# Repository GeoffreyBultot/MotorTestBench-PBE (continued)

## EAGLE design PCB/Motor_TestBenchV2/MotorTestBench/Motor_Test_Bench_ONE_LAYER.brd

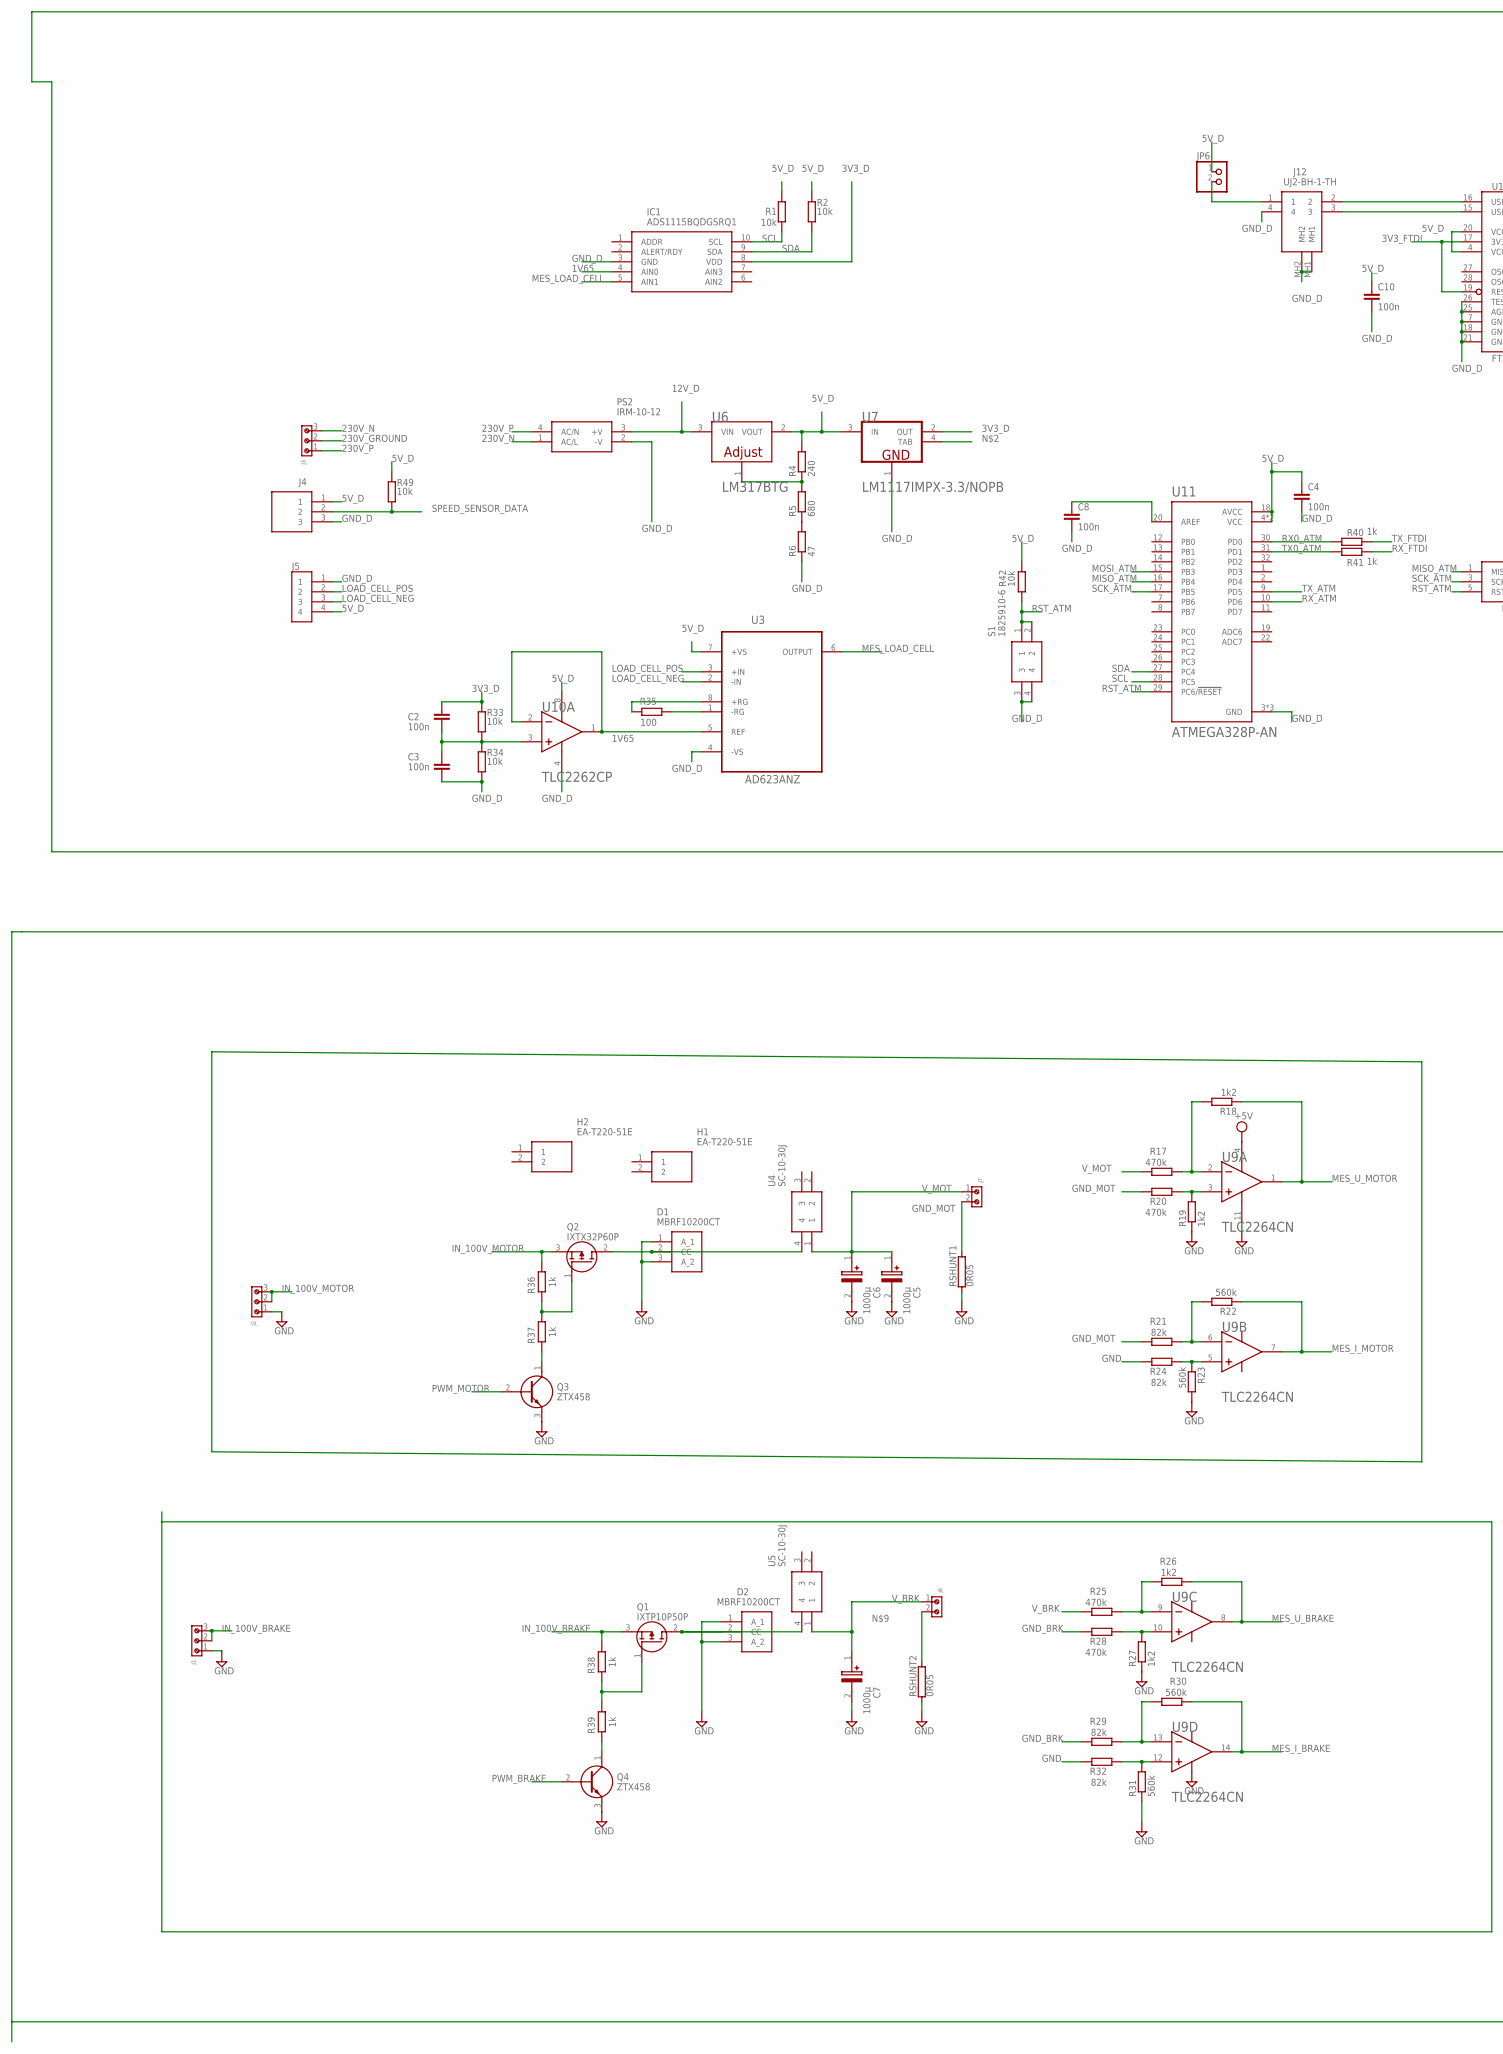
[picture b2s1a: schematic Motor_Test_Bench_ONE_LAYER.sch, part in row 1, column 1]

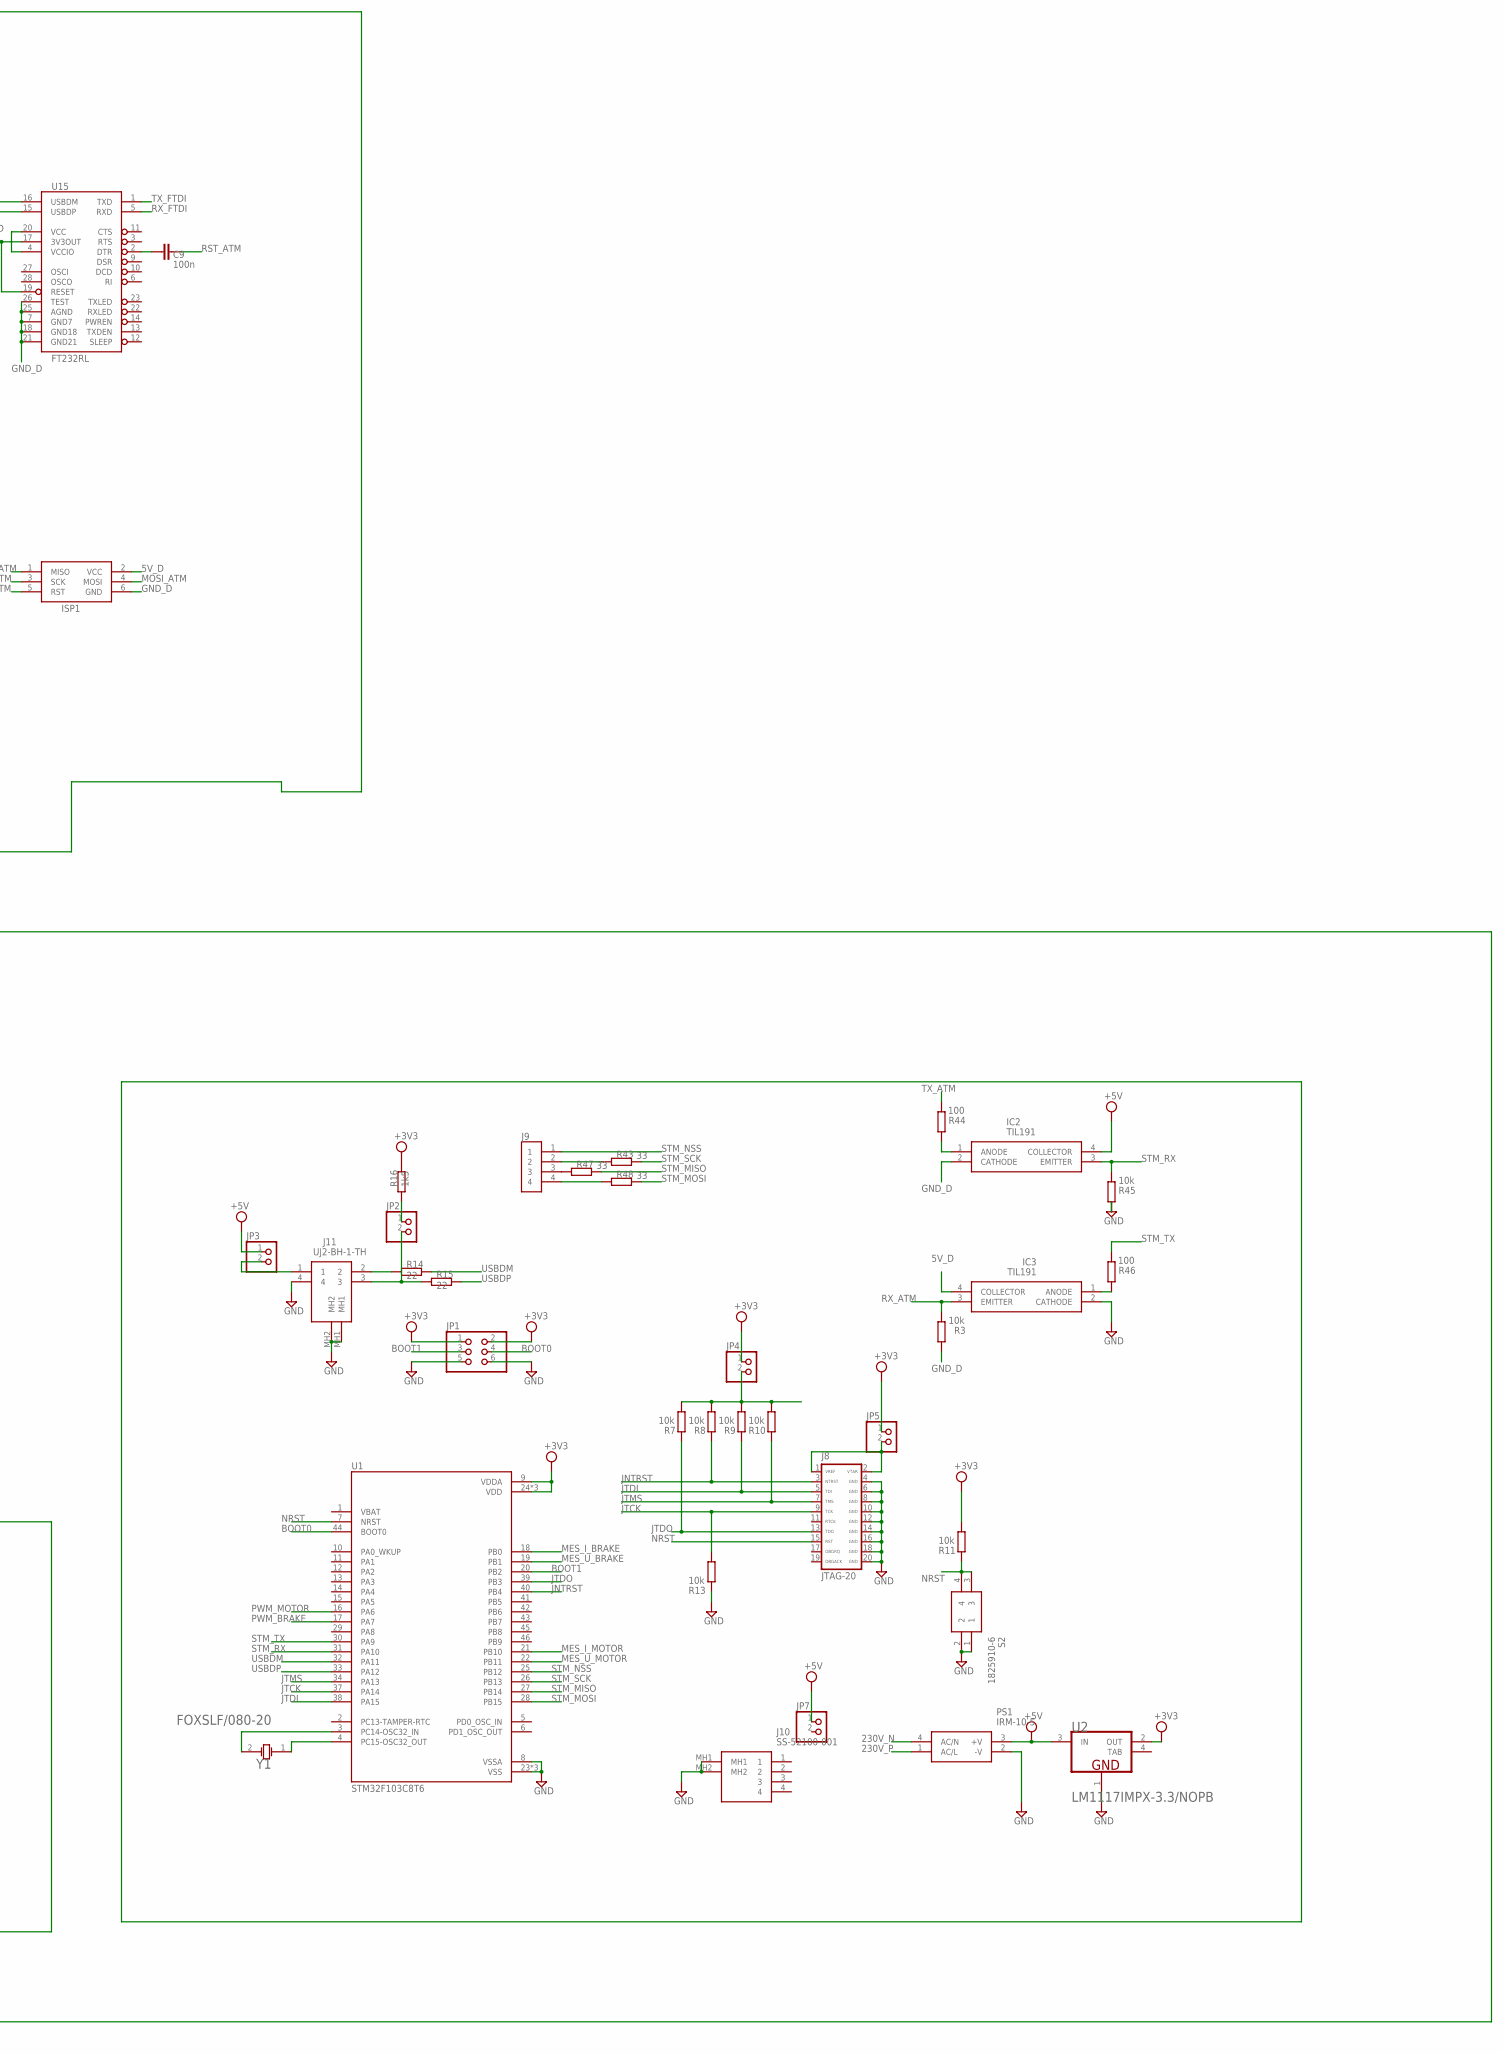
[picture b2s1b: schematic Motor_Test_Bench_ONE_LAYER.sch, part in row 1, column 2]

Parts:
C2, C3: 100n; C0805
C4, C8, C9, C10: 100n; CAP_0805
C5, C6, C7: 1000µ; SLPX102M200C4P3
D1, D2: MBRF10200CT; TO254P490X1000X2143-3P
H1, H2: EA-T220-51E; EAT22051E
IC1: ADS1115BQDGSRQ1; SOP50P490X110-10N
IC2, IC3: TIL191; DIP762W58P254L450H584Q4N
ISP1: AVRISP-6; AVRISP
J1, J2, J3: 691210910003
J4: B3B-XH-A(LF)(SN); SHDR3W64P0X250_1X3_990X575X700
J5, J9: B4B-XH-A(LF)(SN); JST_B4B-XH-A(LF)(SN)
J6, J7: 691210910002
J8: JTAG-20
J10: SS-52100-001; SS52100001
J11, J12: UJ2-BH-1-TH; UJ2BH1TH
JP1: PINHD-2X3; 2X03
JP2, JP3, JP4, JP5, JP6, JP7: PINHD-1X2; 1X02
PS1: IRM-10-5; IRM-10
PS2: IRM-10-12; IRM-10
Q1: IXTP10P50P; TO254P483X1028X1700-3P
Q2: IXTX32P60P; TO545P521X1594X2566-3P
Q3, Q4: ZTX458
R1, R2, R3, R7, R8, R9, R10, R11, R13, R33, R34, R42, R45, R49: 10k; R0805
R4: 240; R0805
R5: 680; R0805
R6: 47; R0805
R14, R15: 22; R0805
R16: 1k5; R0805
R17, R20, R25, R28: 470k; R0805
R18, R19, R26, R27: 1k2; R0805
R21, R24, R29, R32: 82k; R0805
R22, R23, R30, R31: 560k; R0805
R35, R44, R46: 100; R0805
R36, R37, R38, R39, R40, R41: 1k; R0805
R43, R47, R48: 33; R0805
RSHUNT1, RSHUNT2: 0R05; RS05_69-70
S1, S2: 1825910-6
U1: STM32F103C8T6; QFP50P900X900X160-48N
U2, U7: NATIONAL_SEMICONDUCTOR_LM1117IMPX-3.3-NOPBNATIONA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; NATIONAL_SEMICONDUCTOR_LM1117IMPX-3.3-NOPB_2
U3: AD623ANZ; DIP254P762X533-8
U4, U5: SC-10-30J
U6: ON_SEMI_LM317BTGON_SEMI_LM317BTG_0_0; ON_SEMI_LM317BTG_0
U9: TEXAS_INSTRUMENTS_TLC2264CNTEXAS_INSTRUMENTS_TLC2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; TEXAS_INSTRUMENTS_TLC2264CN_0
U10: TEXAS_INSTRUMENTS_TLC2262CPTEXAS_INSTRUMENTS_TLC2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; TEXAS_INSTRUMENTS_TLC2262CP_0
U11: ATMEGA328P-AN; QFP80P900X900X120-32N
U15: FT232RL; SSOP28DB
Y1: FOX_ELECTRONICS_FOXSLF-080-20FOX_ELECTRONICS_FOXS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; FOX_ELECTRONICS_FOXSLF-080-20_0

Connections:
1V65: IC1.4 (AIN0), U3.5 (REF), U10.1 (OUT1), U10.2 (IN1-)
3V3_D: C2.1, IC1.8 (VDD), R33.1, U7.2 (OUT)
3V3_FTDI: U15.17 (3V3OUT), U15.19 (RESET)
5V_D: C4.1, C10.1, IC3.4 (COLLECTOR), ISP1.2 (VCC), J4.1, J5.4, JP6.1, R1.2, R2.2, R4.2, R42.2, R49.1, U3.7 (+VS), U6.2 (VOUT), U7.3 (IN), U10.8 (VDD+), U11.4 (VCC), U11.6 (VCC), U11.18 (AVCC), U15.4 (VCCIO), U15.20 (VCC)
12V_D: PS2.3 (+V), U6.3 (VIN)
230V_GROUND: J3.2
230V_N: J3.3, PS1.4 (AC/N), PS2.1 (AC/L)
230V_P: J3.1, PS1.1 (AC/L), PS2.4 (AC/N)
+3V3: JP1.1, JP1.2, JP4.1, JP5.1, R11.2, R16.1, U1.9 (VDDA), U1.24 (VDD), U1.36 (VDD), U1.48 (VDD), U2.2 (OUT)
+5V: IC2.4 (COLLECTOR), JP3.1, JP7.1, PS1.3 (+V), U2.3 (IN), U9.4 (VDD+)
BOOT0: JP1.4, U1.44 (BOOT0)
BOOT1: JP1.3, U1.20 (PB2)
GND: C5.2 (-), C6.2 (-), C7.2 (-), D1.1 (A_1), D1.3 (A_2), D2.1 (A_1), D2.3 (A_2), IC3.2 (CATHODE), J1.1, J2.1, J8.4 (GND), J8.6 (GND), J8.8 (GND), J8.10 (GND), J8.12 (GND), J8.14 (GND), J8.16 (GND), J8.18 (GND), J8.20 (GND), J10.MH1, J10.MH2, J11.4, J11.MH1, J11.MH2, JP1.5, JP1.6, PS1.2 (-V), Q3.3 (C), Q4.3 (C), R13.1, R19.1, R23.2, R24.2, R27.1, R31.1, R32.2, R45.1, RSHUNT1.1, RSHUNT2.1, S2.1, S2.2, U1.8 (VSSA), U1.23 (VSS), U1.35 (VSS), U1.47 (VSS), U2.1 (GND), U9.11 (VDD-/GND)
GND_BRK: R28.2, R29.2
GND_D: C3.2, C4.2, C8.2, C10.2, IC1.3 (GND), IC2.2 (CATHODE), ISP1.6 (GND), J4.3, J5.1, J12.4, J12.MH1, J12.MH2, PS2.2 (-V), R3.1, R6.1, R34.2, S1.3, S1.4, U3.4 (-VS), U7.1 (GND), U10.4 (VDD-/GND), U11.3 (GND), U11.5 (GND), U11.21 (GND), U15.7 (GND7), U15.18 (GND18), U15.21 (GND21), U15.25 (AGND), U15.26 (TEST)
GND_MOT: J7.2, R20.2, R21.2, RSHUNT1.2
IN_100V_BRAKE: J1.2, J1.3, Q1.3 (S), R38.2
IN_100V_MOTOR: J2.2, J2.3, Q2.3 (S), R36.2
JNTRST: J8.3 (NTRST), R8.1, U1.40 (PB4)
JTCK: J8.9 (TCK), R13.2, U1.37 (PA14)
JTDI: J8.5 (TDI), R9.1, U1.38 (PA15)
JTDO: J8.13 (TDO), R7.1, U1.39 (PB3)
JTMS: J8.7 (TMS), R10.1, U1.34 (PA13)
LOAD_CELL_NEG: J5.3, U3.2 (-IN)
LOAD_CELL_POS: J5.2, U3.3 (+IN)
MES_I_BRAKE: R30.1, U1.18 (PB0), U9.14 (OUT4)
MES_I_MOTOR: R22.1, U1.21 (PB10), U9.7 (OUT2)
MES_LOAD_CELL: IC1.5 (AIN1), U3.6 (OUTPUT)
MES_U_BRAKE: R26.1, U1.19 (PB1), U9.8 (OUT3)
MES_U_MOTOR: R18.1, U1.22 (PB11), U9.1 (OUT1)
MISO_ATM: ISP1.1 (MISO), U11.16 (PB4)
MOSI_ATM: ISP1.4 (MOSI), U11.15 (PB3)
unnamed: D1.2 (CC), Q2.2 (D), U4.4
unnamed: R5.1, R6.2
unnamed: R4.1, R5.2, U6.1 (ADJUST)
unnamed: J11.2, R14.2
unnamed: J11.3, JP2.2, R15.2
unnamed: JP2.1, R16.2
unnamed: J6.2, RSHUNT2.2
unnamed: Q2.1 (G), R36.1, R37.2
unnamed: Q3.1 (E), R37.1
unnamed: R17.1, R18.2, U9.2 (IN1-)
unnamed: R19.2, R20.1, U9.3 (IN1+)
unnamed: C9.2, U15.2 (DTR)
unnamed: C8.1, U11.20 (AREF)
unnamed: Q1.1 (G), R38.1, R39.2
unnamed: R21.1, R22.2, U9.6 (IN2-)
unnamed: R23.1, R24.1, U9.5 (IN2+)
unnamed: R27.2, R28.1, U9.10 (IN3+)
unnamed: R25.1, R26.2, U9.9 (IN3-)
unnamed: R29.1, R30.2, U9.13 (IN4-)
unnamed: Q4.1 (E), R39.1
unnamed: R31.2, R32.1, U9.12 (IN4+)
unnamed: J12.2, U15.16 (USBDM)
unnamed: R35.2, U3.1 (-RG)
unnamed: C2.2, C3.1, R33.2, R34.1, U10.3 (IN1+)
unnamed: R35.1, U3.8 (+RG)
unnamed: J12.3, U15.15 (USBDP)
unnamed: D2.2 (CC), Q1.2 (D), U5.4
unnamed: IC2.1 (ANODE), R44.1
unnamed: IC3.1 (ANODE), R46.1
unnamed: J11.1, JP3.2
unnamed: J8.1 (VREF), J8.2 (VTAR), JP5.2
unnamed: JP4.2, R7.2, R8.2, R9.2, R10.2
unnamed: J12.1, JP6.2
unnamed: J9.2, R43.2
unnamed: J9.3, R47.2
unnamed: J9.4, R48.2
unnamed: U1.4 (PC15-OSC32_OUT), Y1.1
unnamed: U1.3 (PC14-OSC32_IN), Y1.2
NRST: J8.15 (RST), R11.1, S2.3, S2.4, U1.7 (NRST)
PWM_BRAKE: Q4.2 (B), U1.17 (PA7)
PWM_MOTOR: Q3.2 (B), U1.16 (PA6)
RST_ATM: C9.1, ISP1.5 (RST), R42.1, S1.1, S1.2, U11.29 (PC6/!RESET)
RX0_ATM: R40.1, U11.30 (PD0)
RX_ATM: IC3.3 (EMITTER), R3.2, U11.10 (PD6)
RX_FTDI: R41.2, U15.5 (RXD)
SCK_ATM: ISP1.3 (SCK), U11.17 (PB5)
SCL: IC1.10 (SCL), R1.1, U11.28 (PC5)
SDA: IC1.9 (SDA), R2.1, U11.27 (PC4)
SPEED_SENSOR_DATA: J4.2, R49.2
STM_MISO: R47.1, U1.27 (PB14)
STM_MOSI: R48.1, U1.28 (PB15)
STM_NSS: J9.1, U1.25 (PB12)
STM_RX: IC2.3 (EMITTER), R45.2, U1.31 (PA10)
STM_SCK: R43.1, U1.26 (PB13)
STM_TX: R46.2, U1.30 (PA9)
TAB: U2.4 (TAB)
TX0_ATM: R41.1, U11.31 (PD1)
TX_ATM: R44.2, U11.9 (PD5)
TX_FTDI: R40.2, U15.1 (TXD)
USBDM: R14.1, U1.32 (PA11)
USBDP: R15.1, U1.33 (PA12)
V_BRK: C7.1 (+), J6.1, R25.2, U5.1
V_MOT: C5.1 (+), C6.1 (+), J7.1, R17.2, U4.1

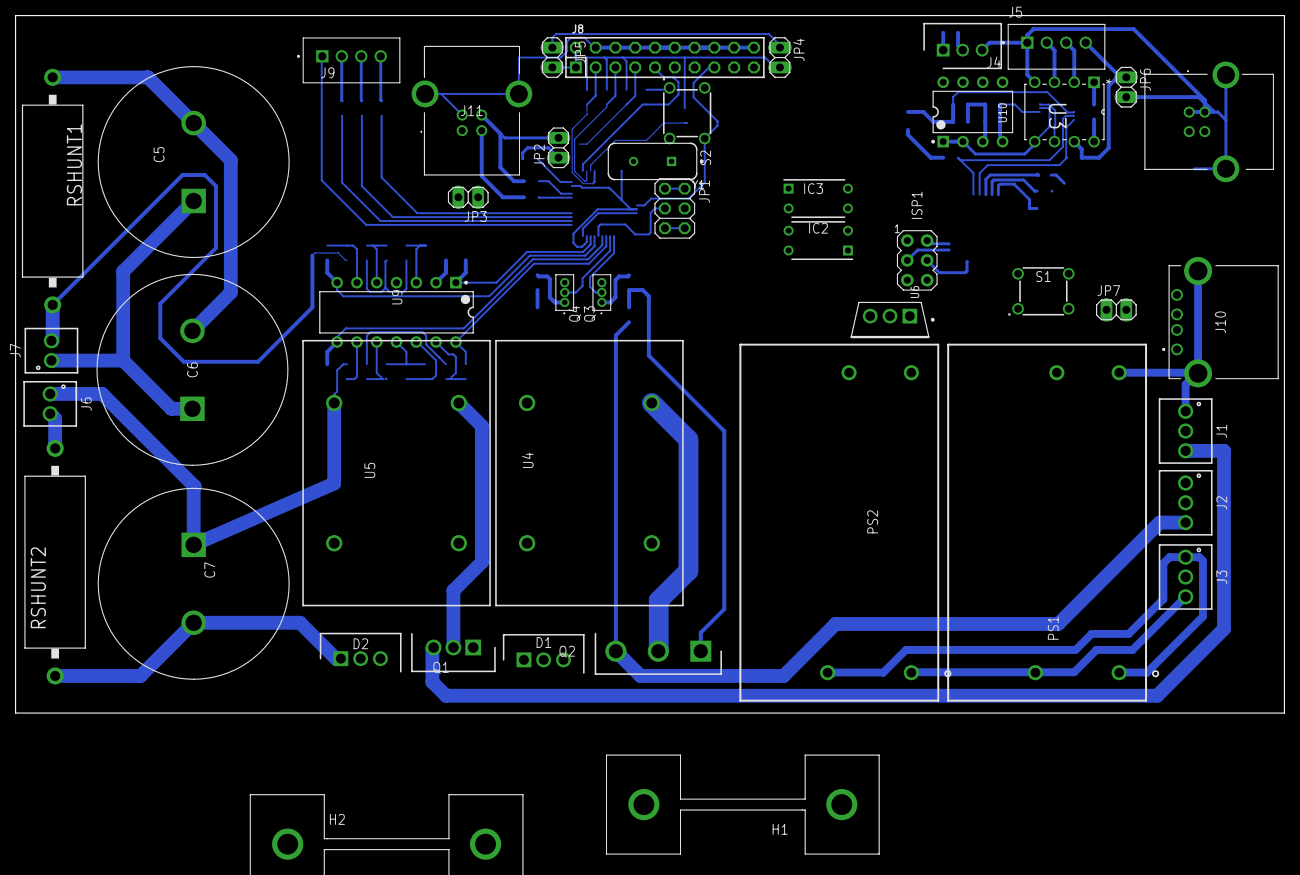
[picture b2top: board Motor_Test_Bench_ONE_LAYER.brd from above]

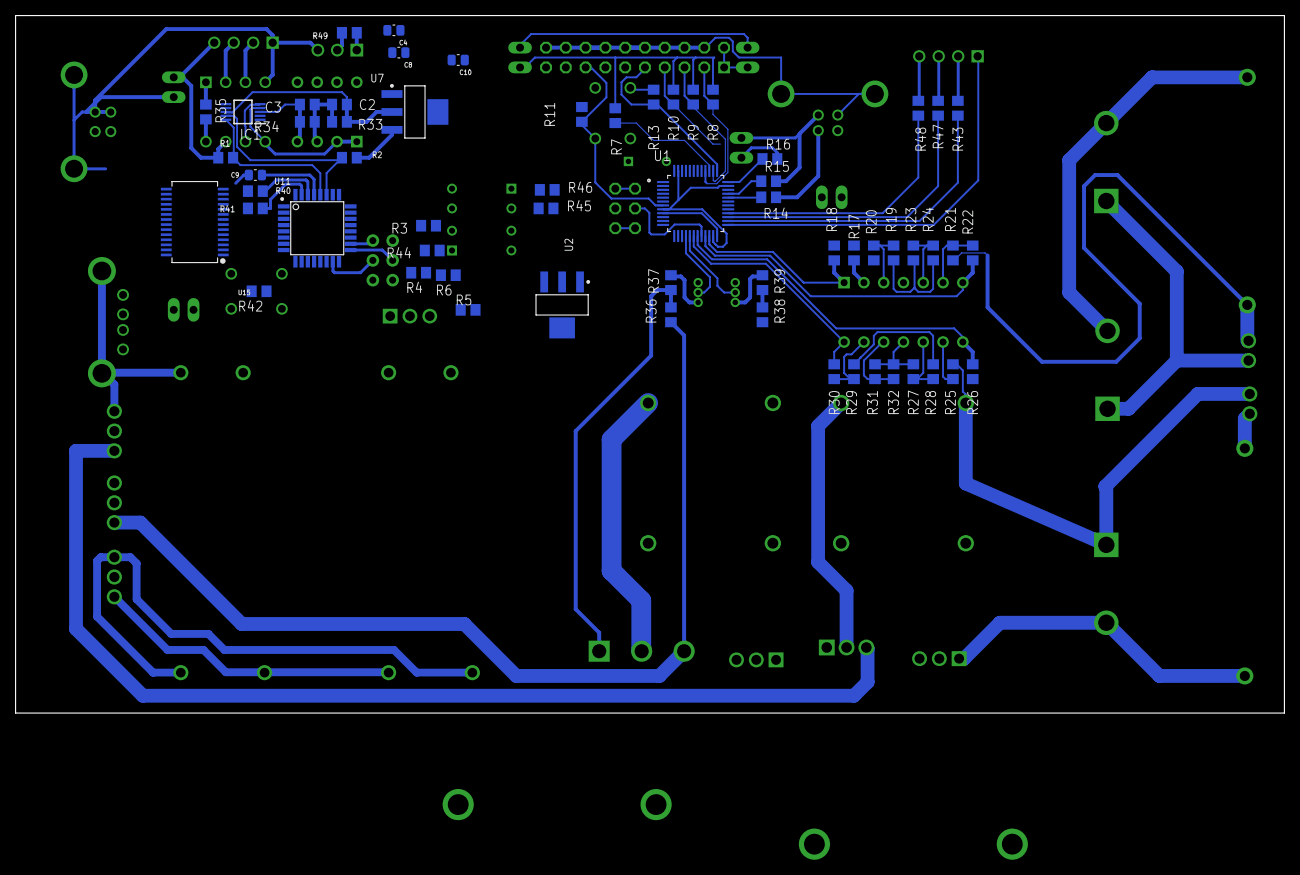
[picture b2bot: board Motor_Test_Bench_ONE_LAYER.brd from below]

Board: 2 copper layers, 162.9 x 89.5 mm, 106 parts (60 on the bottom side), 93 nets.

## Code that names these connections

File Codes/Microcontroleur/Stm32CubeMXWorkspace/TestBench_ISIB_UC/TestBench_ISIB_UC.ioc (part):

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Mcu.Name=STM32F103C(8-B)Tx
Mcu.Package=LQFP48
Mcu.UserName=STM32F103C8Tx
PA0-WKUP.Signal=SharedAnalog_PA0
PA1.Signal=SharedAnalog_PA1
PA10.Mode=Asynchronous
PA10.Signal=USART1_RX
PA11.Mode=Device
PA11.Signal=USB_DM
PA12.Mode=Device
PA12.Signal=USB_DP
PA13.Mode=JTAG_5_pins
PA13.Signal=SYS_JTMS-SWDIO
PA14.Mode=JTAG_5_pins
PA14.Signal=SYS_JTCK-SWCLK
PA15.Mode=JTAG_5_pins
PA15.Signal=SYS_JTDI
PA2.Signal=ADCx_IN2
PA3.Signal=ADCx_IN3
PA4.Mode=NSS_Signal_Hard_Input
PA4.Signal=SPI1_NSS
PA5.Mode=Full_Duplex_Slave
PA5.Signal=SPI1_SCK
PA6.Mode=Full_Duplex_Slave
PA6.Signal=SPI1_MISO
PA7.Mode=Full_Duplex_Slave
PA7.Signal=SPI1_MOSI
PA9.Mode=Asynchronous
PA9.Signal=USART1_TX
PB0.Signal=SharedAnalog_PB0
PB1.Signal=SharedAnalog_PB1
PB11.Signal=GPXTI11
PB3.Mode=JTAG_5_pins
PB3.Signal=SYS_JTDO-TRACESWO
PB4.Mode=JTAG_5_pins
PB4.Signal=SYS_NJTRST
PB6.Mode=I2C
PB6.Signal=I2C1_SCL
PB7.Mode=I2C
PB7.Signal=I2C1_SDA
PB8.Signal=S_TIM4_CH3
PB9.Signal=S_TIM4_CH4
PC14-OSC32_IN.Mode=LSE-External-Oscillator
PC14-OSC32_IN.Signal=RCC_OSC32_IN
PC15-OSC32_OUT.Mode=LSE-External-Oscillator
PC15-OSC32_OUT.Signal=RCC_OSC32_OUT
PD0-OSC_IN.Mode=HSE-External-Oscillator
PD0-OSC_IN.Signal=RCC_OSC_IN
PD1-OSC_OUT.Mode=HSE-External-Oscillator
PD1-OSC_OUT.Signal=RCC_OSC_OUT
RCC.SYSCLKFreq_VALUE=48000000
RCC.SYSCLKSource=RCC_SYSCLKSOURCE_PLLCLK
board=custom

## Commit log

2020-06-06 create repos with all part of the project
2020-06-06 add pcb
2020-06-09 measures correction & add CAO
